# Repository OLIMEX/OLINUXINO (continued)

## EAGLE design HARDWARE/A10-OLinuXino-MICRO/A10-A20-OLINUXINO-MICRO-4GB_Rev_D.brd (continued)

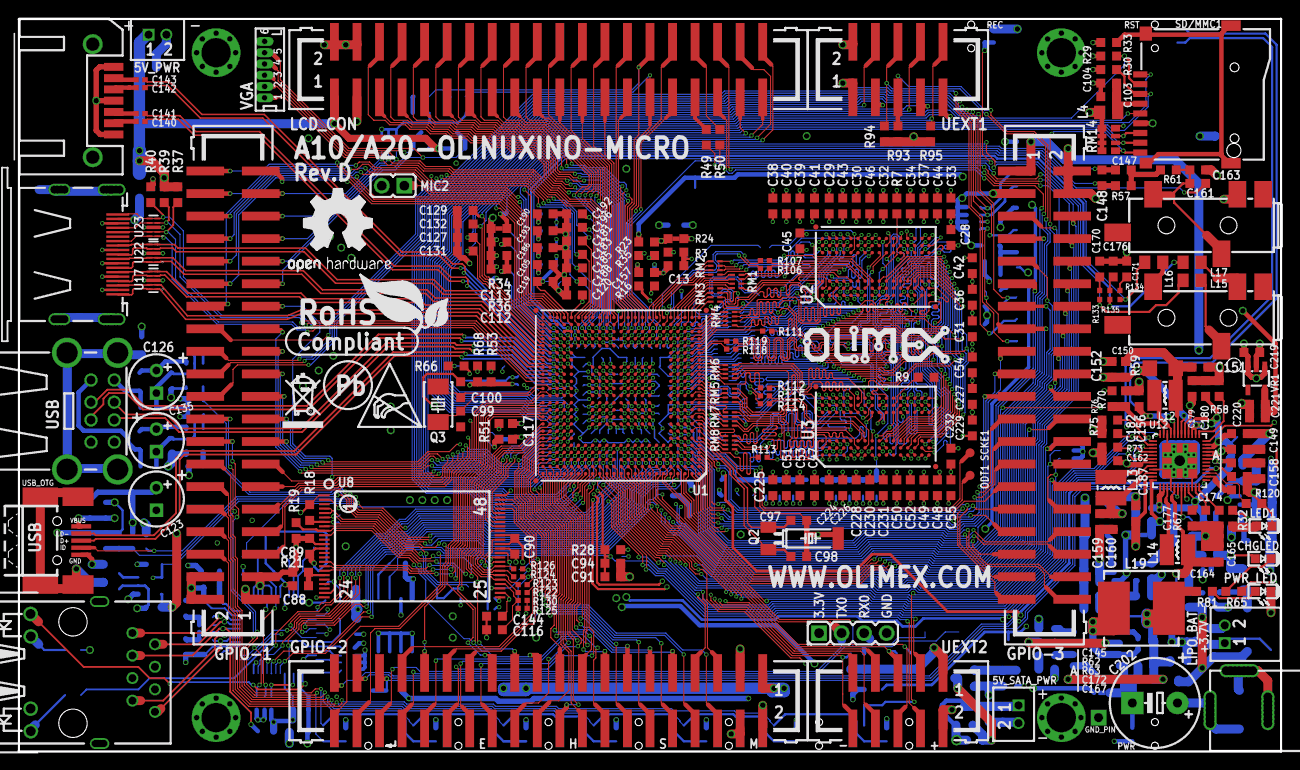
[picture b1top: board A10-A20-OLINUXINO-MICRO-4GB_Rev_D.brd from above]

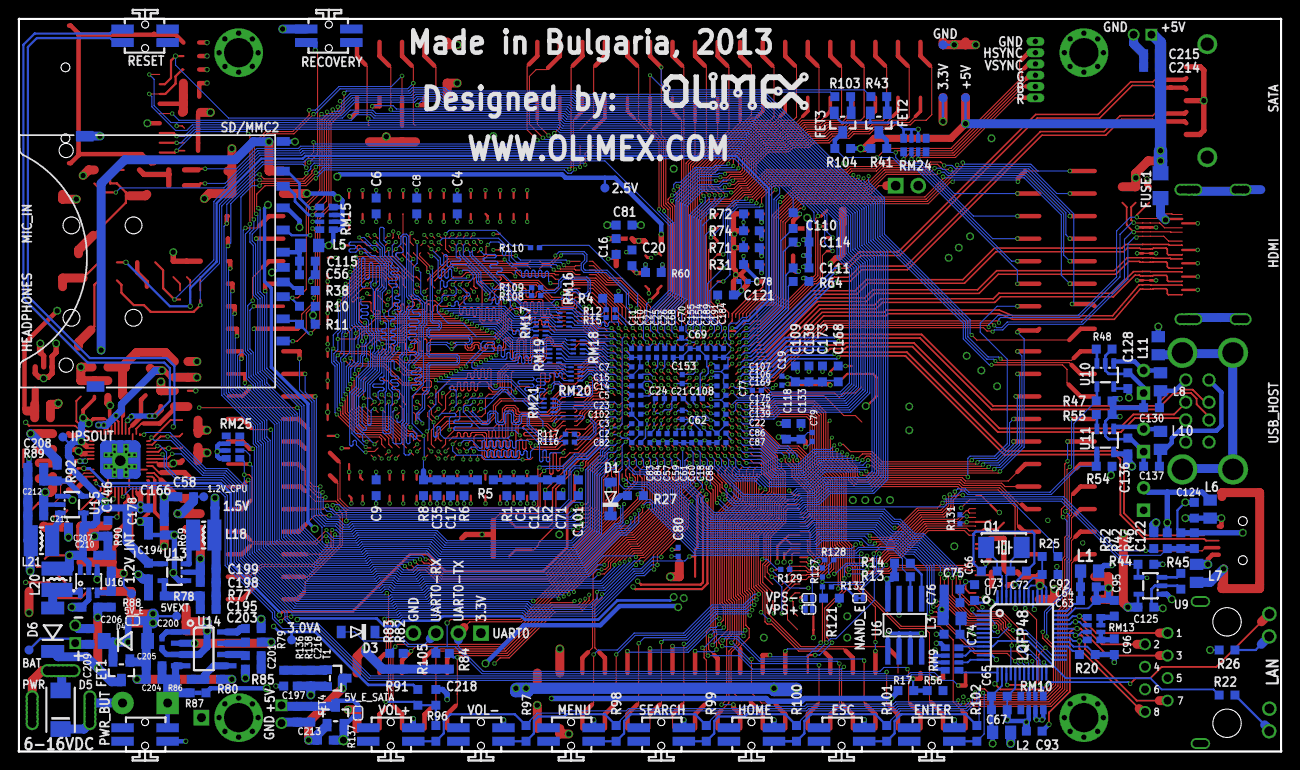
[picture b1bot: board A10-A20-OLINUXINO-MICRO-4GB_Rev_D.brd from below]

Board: 4 copper layers, 142.2 x 82.6 mm, 501 parts (271 on the bottom side), 539 nets.

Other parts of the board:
U$5: LOGO-OPENHARDWARE_8X8
U$6, U$8: OLIMEX1_V
U$9: PB
U$10: ESD_SYMBOL
U$11: RECYCLE_BIN1/8
U$12: ROHS
